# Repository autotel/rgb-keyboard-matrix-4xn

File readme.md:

A 4xn button matrix with ws2812 back-light. Since keyboard keys are not compatible with this type of leds, they are mounted from the back side of the board. For this reason it is unlikely that you can produce the board with a pick and place machine.

This module is meant to be chained together to produce isometric keyboards. A ribbon cable is connected to the microcontroller, and it gets access to 7 rows before needing another connector 

it has not been produced and tested yet.

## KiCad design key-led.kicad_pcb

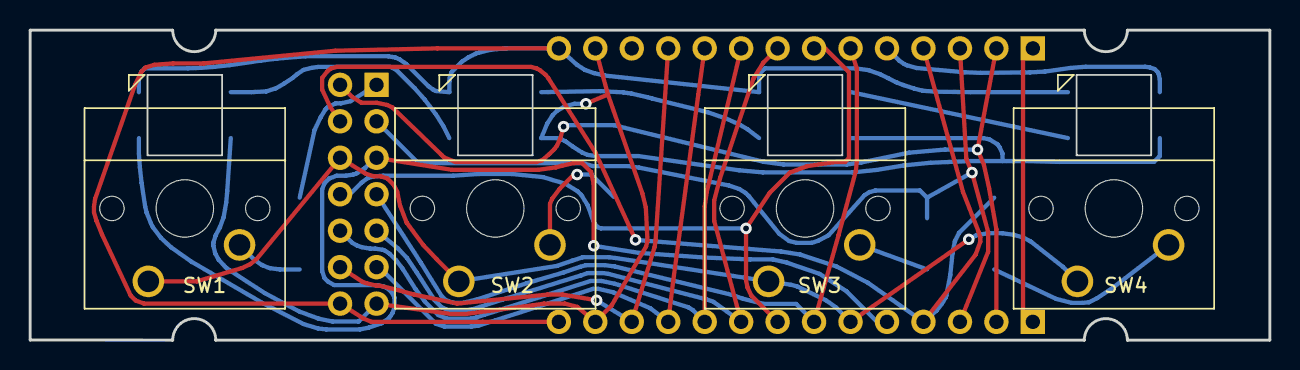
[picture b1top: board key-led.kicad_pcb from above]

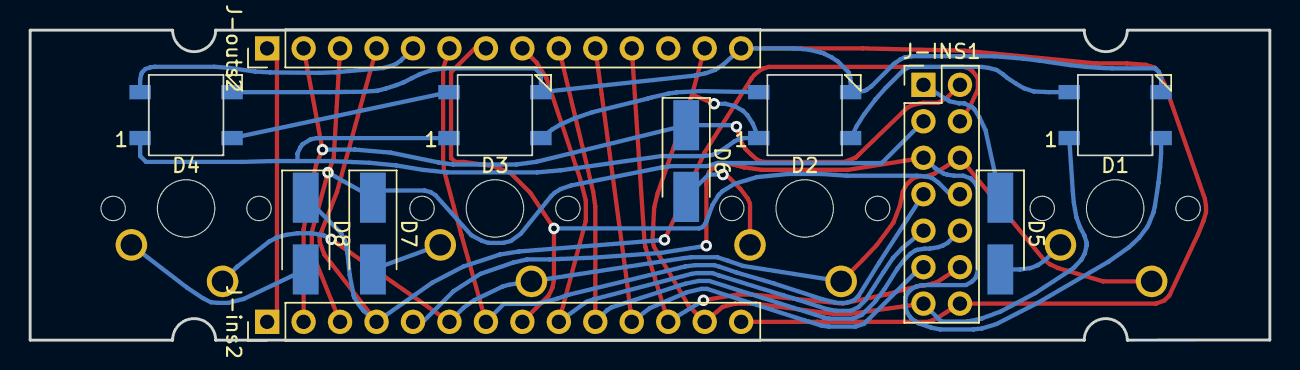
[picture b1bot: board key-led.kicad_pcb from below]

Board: 2 copper layers, 86.4 x 21.6 mm, 15 parts (11 on the bottom side), 22 nets.

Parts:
D1, D2, D3, D4: WS2812B; LED_WS2812B_PLCC4-back-mount
D5, D6, D7, D8: FM4004-W; D_SMA_Handsoldering
J-INS1: Conn_02x07_Odd_Even; PinHeader_2x07_P2.54mm_Vertical
J-ins2: Conn_01x14_Male; PinHeader_1x14_P2.54mm_Vertical
J-outs2: Conn_01x14_Female; PinHeader_1x14_P2.54mm_Vertical
SW1, SW2, SW3, SW4: SW_Push_45deg; SW_Cherry_MX_1.00u_PCB

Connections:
/BUTTON-COL-1: D5.1, J-INS1.1, J-ins2.1, J-outs2.1
/BUTTON-COL-2: D6.1, J-INS1.2, J-ins2.2, J-outs2.2
/BUTTON-COL-3: D7.1, J-INS1.3, J-ins2.3, J-outs2.3
/BUTTON-COL-4: D8.1, J-INS1.4, J-ins2.4, J-outs2.4
/BUTTON-ROW: J-INS1.6, J-ins2.6, SW1.1, SW2.1, SW3.1, SW4.1
/LED-DIN-1: D1.4, J-INS1.5, J-ins2.5
/LED-DOUT-1: D4.2, J-outs2.5
/ROW-UP-IN1: J-INS1.7, J-ins2.7, J-outs2.6
/ROW-UP-IN2: J-INS1.8, J-ins2.8, J-outs2.7
/ROW-UP-IN3: J-INS1.9, J-ins2.9, J-outs2.8
/ROW-UP-IN4: J-INS1.10, J-ins2.10, J-outs2.9
/ROW-UP-IN5: J-INS1.11, J-ins2.11, J-outs2.10
/ROW-UP-IN6: J-INS1.12, J-ins2.12, J-outs2.11
GND: D1.3, D2.3, D3.3, D4.3, J-INS1.14, J-ins2.14, J-outs2.14
unnamed: D1.2, D2.4
unnamed: D2.2, D3.4
unnamed: D3.2, D4.4
unnamed: D5.2, SW1.2
unnamed: D6.2, SW2.2
unnamed: D7.2, SW3.2
unnamed: D8.2, SW4.2
VCC: D1.1, D2.1, D3.1, D4.1, J-INS1.13, J-ins2.13, J-outs2.13

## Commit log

2020-07-07 initial idea for keypad
2020-11-03 4x row design, layout and route
2020-11-03 improve position
2020-11-03 shaped routes in angles, like in the old pcbs
2020-11-03 add readme
